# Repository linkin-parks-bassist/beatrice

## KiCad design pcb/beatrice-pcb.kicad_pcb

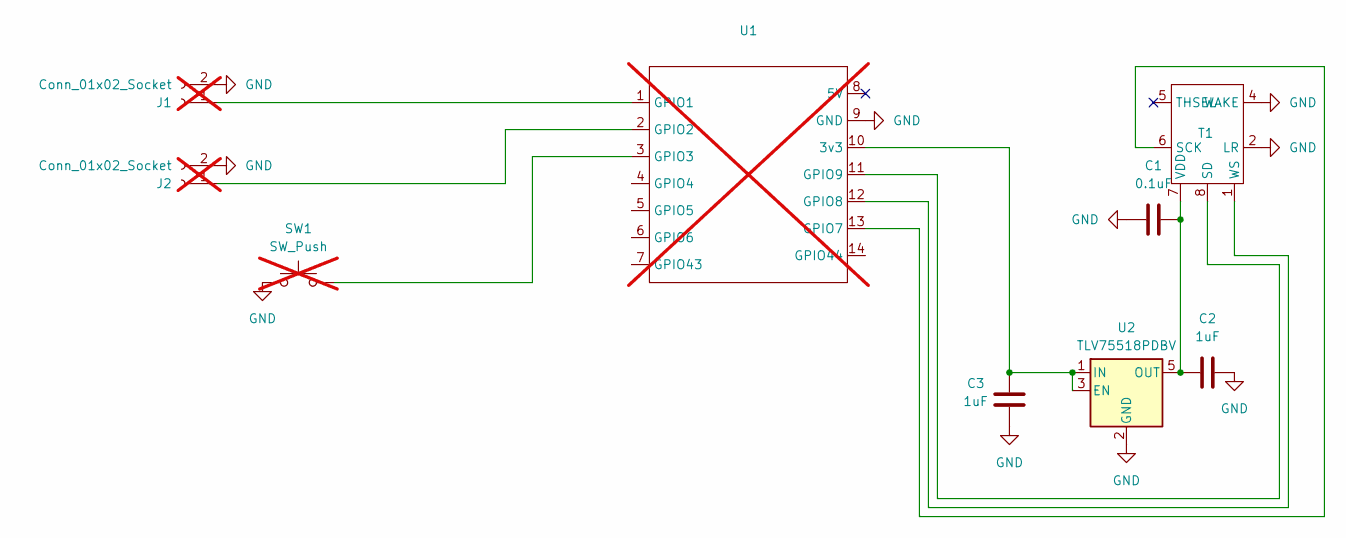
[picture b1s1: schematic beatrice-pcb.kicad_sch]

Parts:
C1: 0.1uF; C_0603_1608Metric
C2, C3: 1uF; C_0603_1608Metric
J1, J2: Conn_01x02_Socket; PinHeader_1x02_P2.54mm_Vertical; not fitted
SW1: SW_Push; SW_PUSH_6mm; not fitted
T1: T5848
U1: Xaio ESP32S3; not fitted
U2: TLV75518PDBV; SOT-23-5

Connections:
GND: C1.1, C2.2, C3.2, J1.2, J2.2, SW1.1, T1.2 (LR), T1.4 (WAKE), U1.9 (GND), U2.2 (GND)
unnamed: J1.1, U1.1 (GPIO1)
unnamed: J2.1, U1.2 (GPIO2)
unnamed: T1.6 (SCK), U1.13 (GPIO7)
unnamed: T1.8 (SD), U1.11 (GPIO9)
unnamed: C1.2, C2.1, T1.7 (VDD), U2.5 (OUT)
unnamed: T1.1 (WS), U1.12 (GPIO8)
unnamed: C3.1, U1.10 (3v3), U2.1 (IN), U2.3 (EN)
unnamed: SW1.2, U1.3 (GPIO3)

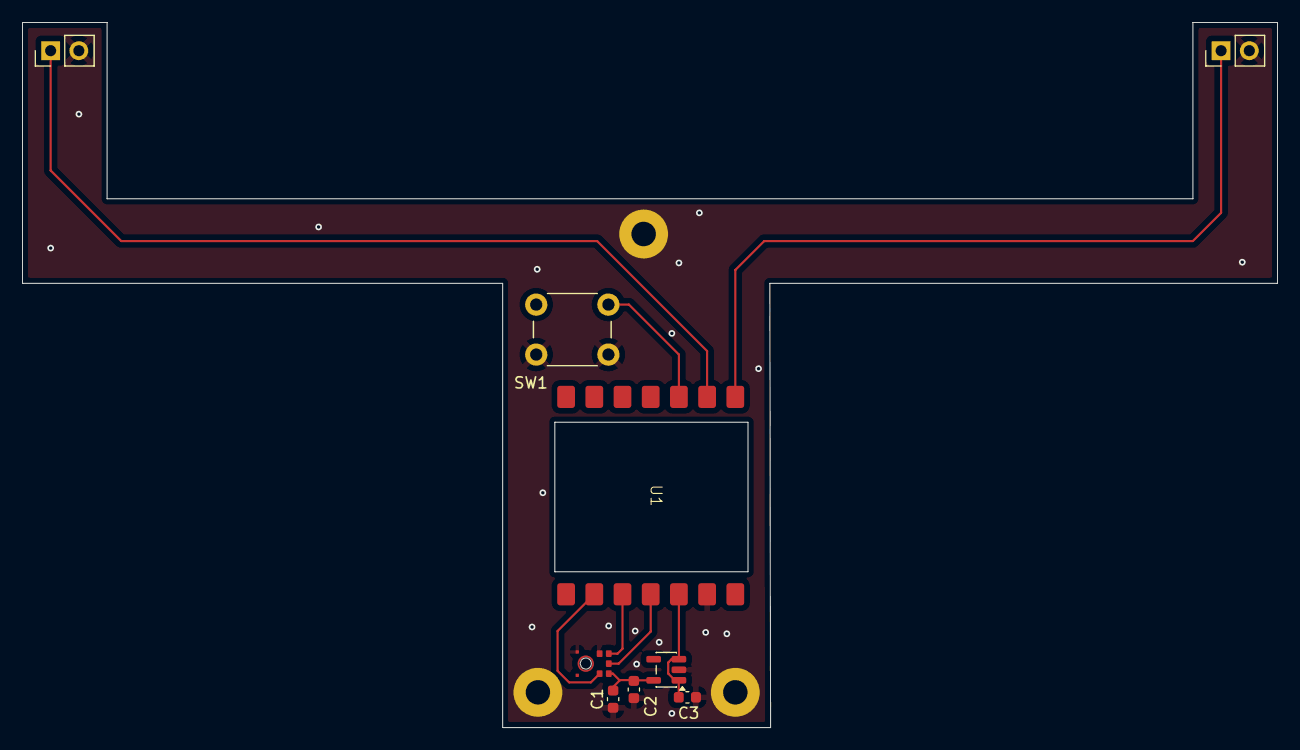
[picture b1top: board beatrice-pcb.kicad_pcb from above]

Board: 2 copper layers, 113.0 x 63.5 mm, 9 parts (0 on the bottom side), 9 nets.

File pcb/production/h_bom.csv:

Designator,Footprint,Quantity,Value,LCSC Part #
C1,0603,1,0.1uF,
"C2, C3",0603,2,1uF,
T1,T5848,1,~,
U2,SOT-23-5,1,TLV75518PDBV,

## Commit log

2026-03-30 Add support for sleep/wake button, + more
2026-03-30 Remove accidental file
2026-05-14 Add PCB
